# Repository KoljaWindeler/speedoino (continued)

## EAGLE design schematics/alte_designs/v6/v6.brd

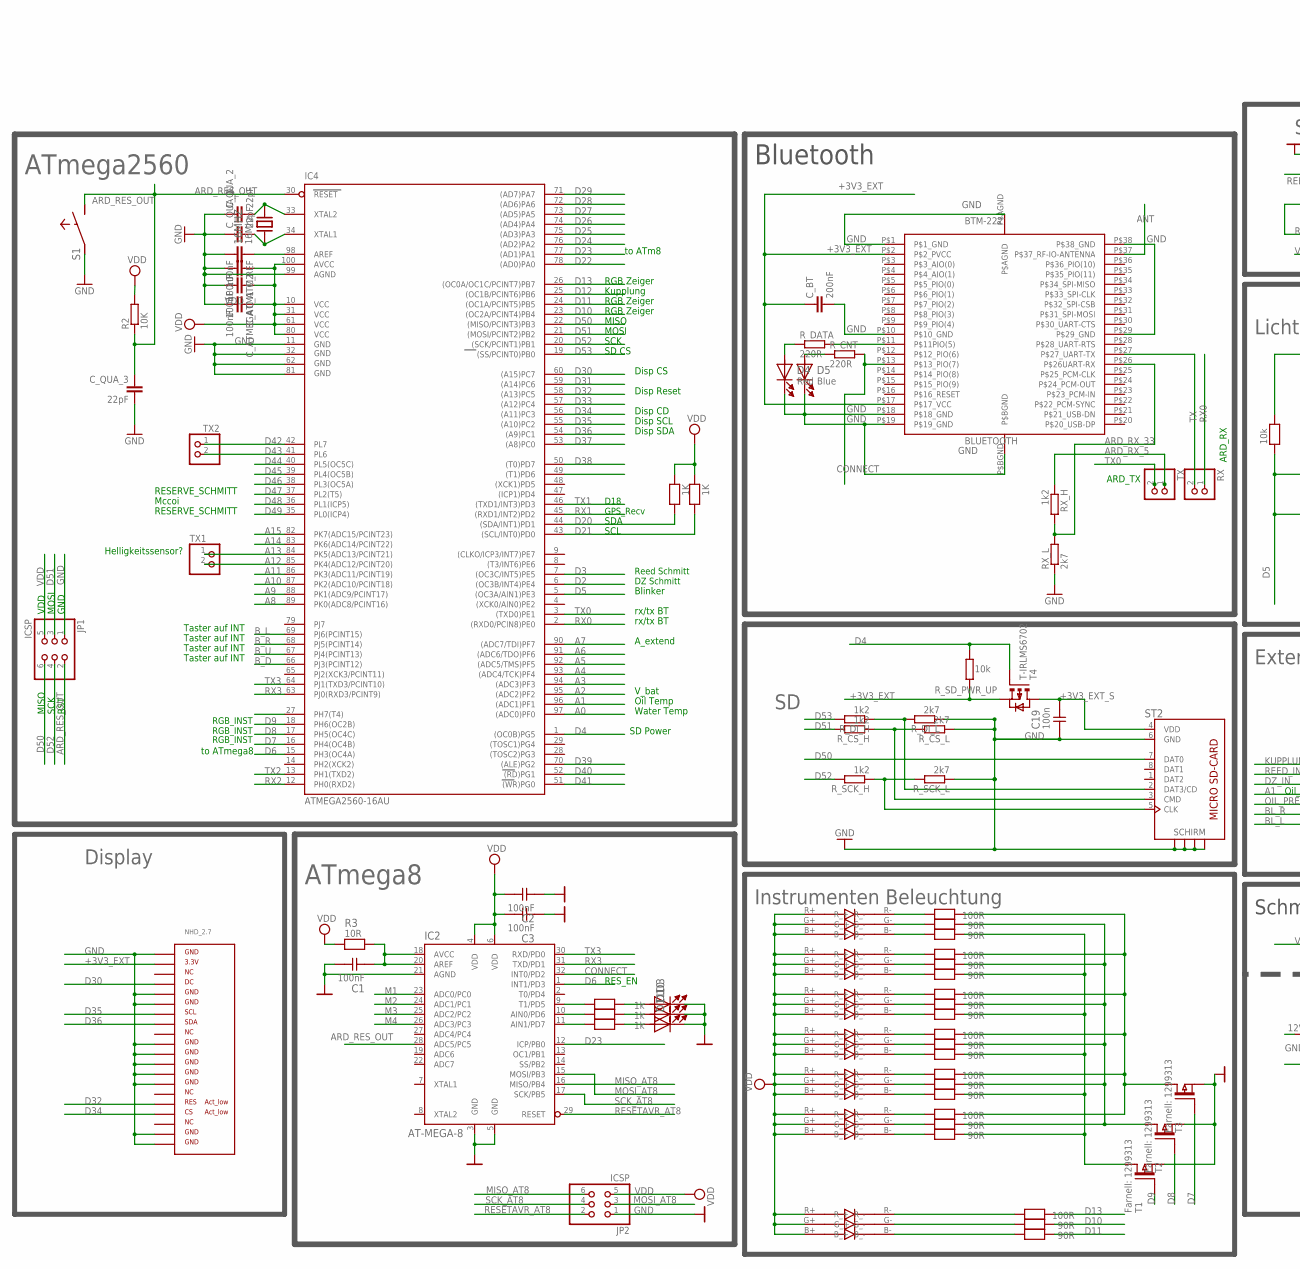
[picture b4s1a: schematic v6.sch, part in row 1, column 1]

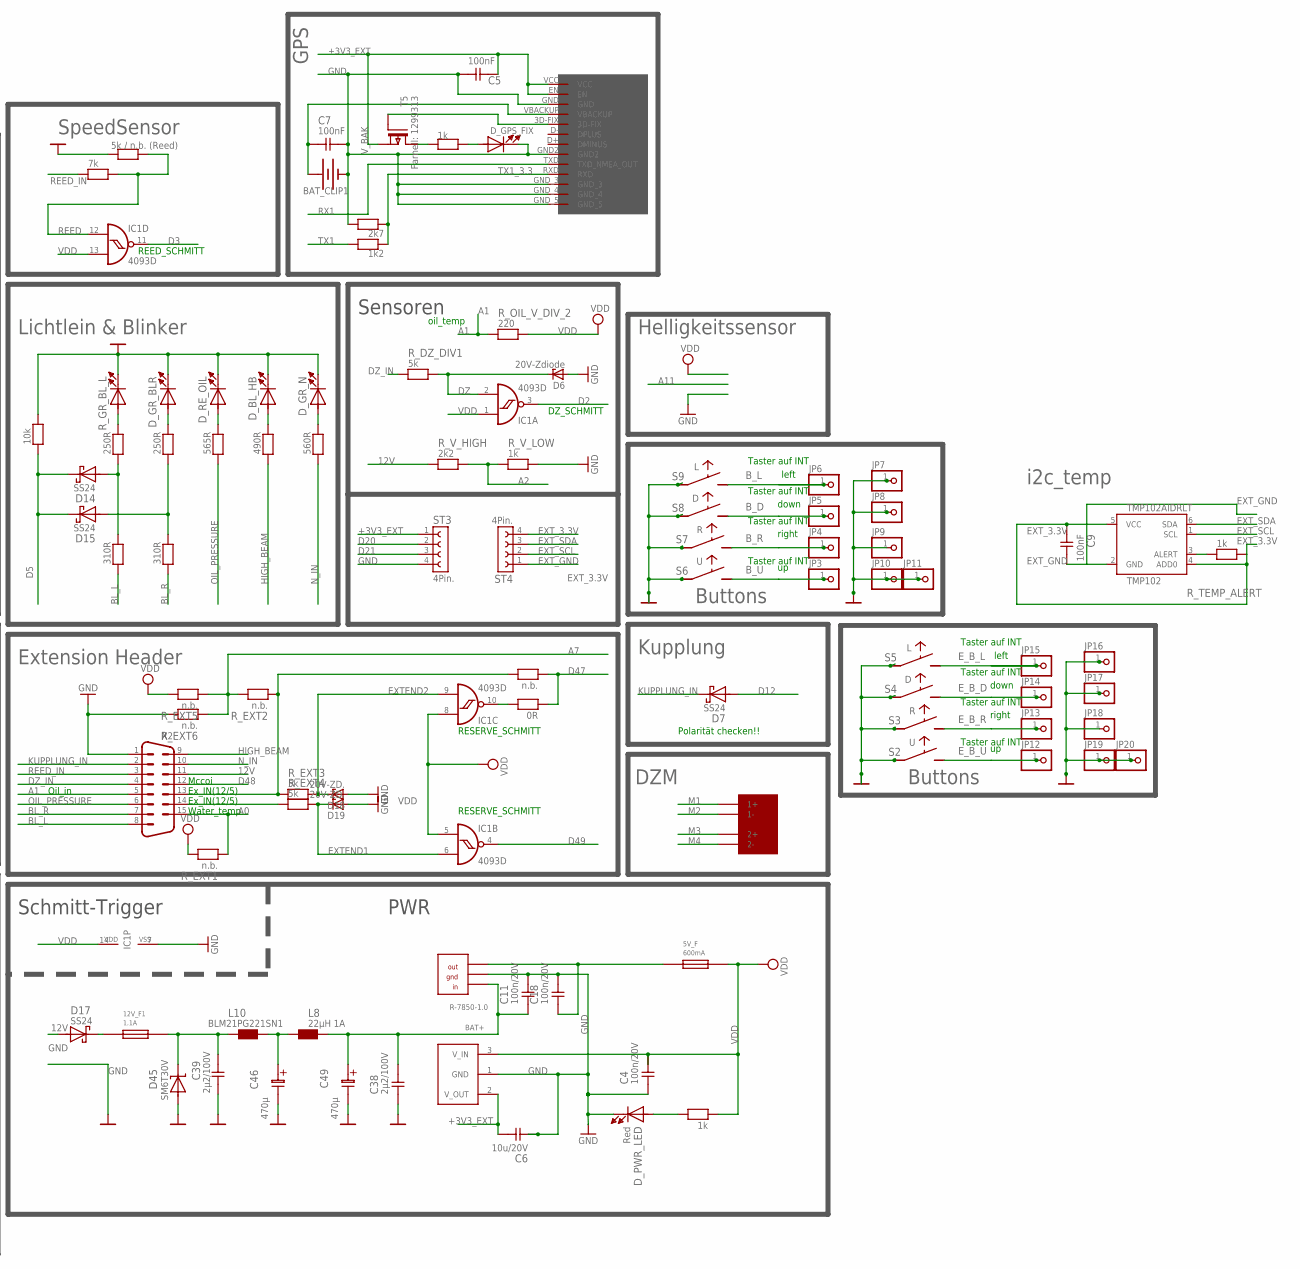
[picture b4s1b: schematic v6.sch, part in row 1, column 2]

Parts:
5V_F: 600mA; POLY_FUSE
12V_F1: 1.1A; POLY_FUSE
16MHZ: 16Mhz; XT-HC49S-SMD
18632422: RGB_LED
BAT_CLIP1: F_908642; BATTCON_12MM
BLUETOOTH: BTM-222
C1, C2, C3, C5, C7, C9: 100nF; 0805
C4, C11, C18: 100n/20V; 0805
C6: 10u/20V; 0805
C19: 100n; 0805
C38, C39: 2µ2/100V; 0805
C46: 470µ; EL-5-8X13R
C49: 470µ; EL-5-8X13
C_ATM1, C_ATM2: 100nF; C0805
C_ATMEGA: 100nF; C0805
C_BT: 200nF; C0805
C_QUA_1, C_QUA_2, C_QUA_3: 22pF; C0805
C_REF: 100nF; C0805
D3, D10, D11: LED0805; LED-0805
D4: Red; LED-0805
D5: Blue; LED-0805
D6: 20V-Zdiode; SMB
D7, D14, D15, D17: SS24; SMB
D18, D19: 20V-ZD.; SMB
D45: SM6T30V; SMB
DCDC53.3: AP1117E33G; SOT223
D_BL_HB: HighB _ 645-598-8191-107F; LED-0805
D_GPS_FIX: Red; LED-0805
D_GR_BLR: BL_R; LED-0805
D_GR_N: N _ M 645-598-8110-107F; LED-0805
D_PWR_LED: Red; LED-0805
D_RE_OIL: OIL M 645-598-8110-107F; LED-0805
GPS: MT3329
IC1: 4093D; SO14
IC2: AT-MEGA-8; TQFP-32_7X7
IC4: ATMEGA2560-16AU; TQFP100
JP1, JP2: ICSP; 2X03
JP3, JP4, JP5, JP6, JP7, JP8, JP9, JP10, JP11, JP12, JP13, JP14, JP15, JP16, JP17, JP18, JP19, JP20: PINHD-1X1; 1X01
L8: 22µH 1A; L-PD54
L10: BLM21PG221SN1; 0805+603
NHD_2.7: NHD_2.7_SOLO_RO
PWR_R78: R-7805-1.0; SIP3
R1, R4: 250R; 0805
R2: 10K; R0805
R3: 10R; 0805
R5: 565R; 0805
R6: 490R; 0805
R7, R8: 310R; 0805
R9: 10k; 0805
R10: 5k / n.b. (Reed); 0805
R11: 7k; 0805
R12, R18, R21, R24, R29, R32, R35: 100R; 0805
R13, R14, R19, R20, R22, R23, R25, R26, R30, R31, R33, R34, R36, R37: 90R; 0805
R15, R16, R17, R28: 1k; 0805
R27: 560R; 0805
R38: 0R; 0805
R39: n.b.; 0805
R40: 2k7; 0805
R41: 1k2; 0805
RX: PINHD-1X2; 1X02
RX_H: 1k2; M0805
RX_L: 2k7; M0805
R_CNT: 220R; M0805
R_CS_H: 1k2; M0805
R_CS_L: 2k7; M0805
R_DATA: 220R; M0805
R_DI_H: 1k2; M0805
R_DI_L: 2k7; M0805
R_DZ_DIV1: 5k; 0805
R_EXT1, R_EXT2, R_EXT5, R_EXT6: n.b.; 0805
R_EXT3, R_EXT4: 5k; 0805
R_GR_BL_L: BL_L; LED-0805
R_LED_5V: 1k; 0805
R_OIL_V_DIV_2: 220; 0805
R_SCK_H: 1k2; M0805
R_SCK_L: 2k7; M0805
R_SCL_UP: 1K; 0805
R_SDA_UP: 1K; 0805
R_SD_PWR_UP: 10k; M0805
R_TEMP_ALERT: 1k; 0805
R_V_HIGH: 2k2; 0805
R_V_LOW: 1k; 0805
S1: SW-TASTERECO-DIAGONAL; SW-ECO
S2, S6: U; SW-ECO
S3, S7: R; SW-ECO
S4, S8: D; SW-ECO
S5, S9: L; SW-ECO
ST2: SD_MICRO
ST3, ST4: BU_1X4_BL17-SMD; BL17SMD_1X4
T1, T2, T3, T5: Farnell: 1299313; SOT-23
T4: T-IRLMS6702; SOT-23-6
TMP102AIDRLT: TMP102; SOT563
TX, TX1, TX2: PINHD-1X2; 1X02
U$3: STEPPER
U$14, U$15, U$16, U$18, U$19, U$20: RGB_LED
X2: SUB-D-IP67; IP67-SUB-D

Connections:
12V: D17.A, R_V_HIGH.1, X2.11
12V_SAFE: 12V_F1.P$2, C39.1, D45.K, L10.1
+3V3_EXT: BLUETOOTH.P$2 (P$2_PVCC), BLUETOOTH.P$17 (P$17_VCC), C5.2, C6.2, C_BT.1, DCDC53.3.2 (V_OUT), GPS.EN, GPS.VCC, NHD_2.7.VDD0 (VDD), R_SD_PWR_UP.2, ST3.1, T4.4 (S), T5.2 (S)
+3V3_EXT_S: C19.2, ST2.4 (VDD), T4.1 (D1), T4.2 (D2), T4.5 (D3), T4.6 (D4)
A0: IC4.97 ((ADC0)PF0), R_EXT1.1, X2.15
A1: IC4.96 ((ADC1)PF1), R_OIL_V_DIV_2.1, X2.5
A2: IC4.95 ((ADC2)PF2), R_V_HIGH.2, R_V_LOW.1
A3: IC4.94 ((ADC3)PF3)
A4: IC4.93 ((ADC4/TCK)PF4)
A5: IC4.92 ((ADC5/TMS)PF5)
A6: IC4.91 ((ADC6/TDO)PF6)
A7: IC4.90 ((ADC7/TDI)PF7), R_EXT2.2, R_EXT5.1, R_EXT6.1
A8: IC4.89 (PK0(ADC8/PCINT16))
A9: IC4.88 (PK1(ADC9/PCINT17))
A10: IC4.87 (PK2(ADC10/PCINT18))
A11: IC4.86 (PK3(ADC11/PCINT19))
A12: IC4.85 (PK4(ADC12/PCINT20)), TX1.2
A13: IC4.84 (PK5(ADC13/PCINT21)), TX1.1
A14: IC4.83 (PK6(ADC14/PCINT22))
A15: IC4.82 (PK7(ADC15/PCINT23))
ANT: BLUETOOTH.P$37 (P$37_RF-IO-ANTENNA)
ARD_RES_OUT: C_QUA_3.1, IC2.28 (ADC5/PC5), IC4.30 (RESET), JP1.2, R2.1, S1.4 (2)
ARD_RX_5: RX_H.1, TX.1
ARD_RX_33: BLUETOOTH.P$26 (P$26UART-RX), RX_H.2, RX_L.2
BAT+: C11.1, C38.2, C49.1, L8.2, PWR_R78.IN
BLUE_INSTR: R14.2, R20.2, R23.2, R31.2, R34.2, R37.2, T1.3 (D)
BL_L: R8.1, X2.8
BL_R: R7.1, X2.7
B_D: IC4.66 (PJ3(PCINT12)), JP5.1, S8.4 (2)
B_L: IC4.69 (PJ6(PCINT15)), JP6.1, S9.4 (2)
B_R: IC4.68 (PJ5(PCINT14)), JP4.1, S7.4 (2)
B_U: IC4.67 (PJ4(PCINT13)), JP3.1, S6.4 (2)
CONNECT: BLUETOOTH.P$13 (P$13_PIO(7)), IC2.32 (INT0/PD2), R_CNT.2
D2: IC1.3 (O), IC4.6 ((OC3B/INT4)PE4)
D3: IC1.11 (O), IC4.7 ((OC3C/INT5)PE5)
D4: IC4.1 ((OC0B)PG5), R_SD_PWR_UP.1, T4.3 (G)
D5: D14.K, D15.K, IC4.5 ((OC3A/AIN1)PE3), R9.2
D6: IC2.1 (INT1/PD3), IC4.15 (PH3(OC4A))
D7: IC4.16 (PH4(OC4B)), T3.1 (G)
D8: IC4.17 (PH5(OC4C)), T2.1 (G)
D9: IC4.18 (PH6(OC2B)), T1.1 (G)
D10: IC4.23 ((OC2A/PCINT4)PB4), R25.2
D11: IC4.24 ((OC1A/PCINT5)PB5), R26.2
D12: D7.A, IC4.25 ((OC1B/PCINT6)PB6)
D13: IC4.26 ((OC0A/OC1C/PCINT7)PB7), R24.2
D20: IC4.44 ((SDA/INT1)PD1), R_SDA_UP.2, ST3.2
D21: IC4.43 ((SCL/INT0)PD0), R_SCL_UP.2, ST3.3
D22: IC4.78 ((AD0)PA0)
D23: IC2.12 (ICP/PB0), IC4.77 ((AD1)PA1)
D24: IC4.76 ((AD2)PA2)
D25: IC4.75 ((AD3)PA3)
D26: IC4.74 ((AD4)PA4)
D27: IC4.73 ((AD5)PA5)
D28: IC4.72 ((AD6)PA6)
D29: IC4.71 ((AD7)PA7)
D30: IC4.60 ((A15)PC7), NHD_2.7.DC
D31: IC4.59 ((A14)PC6)
D32: IC4.58 ((A13)PC5), NHD_2.7.RES
D33: IC4.57 ((A12)PC4)
D34: IC4.56 ((A11)PC3), NHD_2.7.CS
D35: IC4.55 ((A10)PC2), NHD_2.7.SCLK (SCL)
D36: IC4.54 ((A9)PC1), NHD_2.7.SDIN (SDA)
D37: IC4.53 ((A8)PC0)
D38: IC4.50 ((T0)PD7)
D39: IC4.70 ((ALE)PG2)
D40: IC4.52 ((RD)PG1)
D41: IC4.51 ((WR)PG0)
D42: IC4.42 (PL7), TX2.1
D43: IC4.41 (PL6), TX2.2
D44: IC4.40 (PL5(OC5C))
D45: IC4.39 (PL4(OC5B))
D46: IC4.38 (PL3(OC5A))
D47: IC4.37 (PL2(T5)), R38.2, R39.2
D48: IC4.36 (PL1(ICP5)), X2.12
D49: IC1.4 (O), IC4.35 (PL0(ICP4))
D50: IC4.22 ((MISO/PCINT3)PB3), JP1.6, ST2.7 (DAT0)
D51: IC4.21 ((MOSI/PCINT2)PB2), JP1.3, R_CS_H.2
D52: IC4.20 ((SCK/PCINT1)PB1), JP1.4, R_SCK_H.2
D53: IC4.19 ((SS/PCINT0)PB0), R_DI_H.2
DZ: D6.C, IC1.2 (I1), R_DZ_DIV1.2
DZ_IN: R_DZ_DIV1.1, X2.4
EXTEND1: D19.C, IC1.6 (I1), R_EXT4.2
EXTEND2: D18.C, IC1.9 (I1), R_EXT3.2
EXT_3.3V: C9.1, R_TEMP_ALERT.2, ST4.4, TMP102AIDRLT.4 (ADD0), TMP102AIDRLT.5 (VCC)
EXT_GND: C9.2, ST4.1, TMP102AIDRLT.2 (GND)
EXT_SCL: ST4.2, TMP102AIDRLT.1 (SCL)
EXT_SDA: ST4.3, TMP102AIDRLT.6 (SDA)
E_B_D: JP14.1, S4.4 (2)
E_B_L: JP15.1, S5.4 (2)
E_B_R: JP13.1, S3.4 (2)
E_B_U: JP12.1, S2.4 (2)
E_GND: JP16.1, JP17.1, JP18.1, JP19.1, JP20.1, S2.1, S3.1, S4.1, S5.1
GND: BAT_CLIP1.GND (-), BLUETOOTH.P$1 (P$1_GND), BLUETOOTH.P$10 (P$10_GND), BLUETOOTH.P$18 (P$18_GND), BLUETOOTH.P$19 (P$19_GND), BLUETOOTH.P$29 (P$29_GND), BLUETOOTH.P$38 (P$38_GND), BLUETOOTH.P$AGND, BLUETOOTH.P$BGND, C1.2, C2.1, C3.1, C4.1, C5.1, C6.1, C7.2, C11.2, C18.2, C19.1, C38.1, C39.2, C46.2, C49.2, C_ATM1.2, C_ATM2.2, C_ATMEGA.2, C_BT.2, C_QUA_1.1, C_QUA_2.1, C_QUA_3.2, C_REF.2, D3.2 (K), D4.2 (K), D5.2 (K), D6.A, D10.2 (K), D11.2 (K), D18.A, D19.A, D45.A, DCDC53.3.1 (GND), D_BL_HB.2 (K), D_GPS_FIX.2 (K), D_GR_BLR.2 (K), D_GR_N.2 (K), D_PWR_LED.2 (K), D_RE_OIL.2 (K), GPS.GND, GPS.GND2, GPS.GND_3, GPS.GND_4, GPS.GND_5, IC1.7 (VSS), IC2.3 (GND), IC2.5 (GND), IC2.21 (AGND), IC4.11 (GND), IC4.32 (GND1), IC4.62 (GND2), IC4.81 (GND3), IC4.99 (AGND), JP1.1, JP2.1, JP7.1, JP8.1, JP9.1, JP10.1, JP11.1, NHD_2.7.GND0 (GND), NHD_2.7.GND1 (GND2), NHD_2.7.GND2 (GND3), NHD_2.7.GND3 (GND4), NHD_2.7.GND4 (GND5), NHD_2.7.GND5 (GND6), NHD_2.7.GND6 (GND7), NHD_2.7.GND7 (GND8), NHD_2.7.GND8 (GND9), NHD_2.7.GND9 (GND10), PWR_R78.GND, R9.1, R10.2, R40.2, RX_L.1, R_CS_L.1, R_DI_L.1, R_EXT6.2, R_GR_BL_L.2 (K), R_SCK_L.1, R_V_LOW.2, S1.1, S6.1, S7.1, S8.1, S9.1, ST2.6 (GND), ST2.GND (SCHIRM1), ST2.GND2 (SCHIRM2), ST2.GND3 (SCHIRM3), ST2.GND4 (SCHIRM), ST3.4, T1.2 (S), T2.2 (S), T3.2 (S), X2.1
GREEN_INSTR: R13.2, R19.2, R22.2, R30.2, R33.2, R36.2, T2.3 (D)
HIGH_BEAM: R6.1, X2.9
KUPPLUNG_IN: D7.K, X2.2
M1: IC2.23 (ADC0/PC0), U$3.1+
M2: IC2.24 (ADC1/PC1), U$3.1-
M3: IC2.25 (ADC2/PC2), U$3.2+
M4: IC2.26 (ADC3/PC3), U$3.2-
MISO_AT8: IC2.16 (MISO/PB4), JP2.6
MOSI_AT8: IC2.15 (MOSI/PB3), JP2.3
unnamed: C46.1, L8.1, L10.2
unnamed: D14.A, R1.1, R8.2
unnamed: C1.1, IC2.18 (AVCC), IC2.20 (AREF), R3.2
unnamed: R_TEMP_ALERT.1, TMP102AIDRLT.3 (ALERT)
unnamed: D5.1 (A), R_CNT.1
unnamed: R31.1, U$18.B- (B_-)
unnamed: R30.1, U$18.G- (G_-)
unnamed: R29.1, U$18.R- (R_-)
unnamed: D_PWR_LED.1 (A), R_LED_5V.2
unnamed: R34.1, U$16.B- (B_-)
unnamed: D15.A, R4.1, R7.2
unnamed: D4.1 (A), R_DATA.1
unnamed: R_CS_H.1, R_CS_L.2, ST2.3 (CMD)
unnamed: IC2.11 (AIN1/PD7), R17.1
unnamed: D_GPS_FIX.1 (A), R28.2
unnamed: GPS.3D-FIX, T5.1 (G)
unnamed: R28.1, T5.3 (D)
unnamed: IC2.10 (AIN0/PD6), R16.1
unnamed: 5V_F.P$1, C18.1, PWR_R78.OUT
unnamed: IC2.9 (T1/PD5), R15.1
unnamed: R33.1, U$16.G- (G_-)
unnamed: R32.1, U$16.R- (R_-)
unnamed: R_SCK_H.1, R_SCK_L.2, ST2.5 (CLK)
unnamed: 12V_F1.P$1, D17.K
unnamed: R_DI_H.1, R_DI_L.2, ST2.2 (DAT3/CD)
unnamed: R37.1, U$14.B- (B_-)
unnamed: R36.1, U$14.G- (G_-)
unnamed: R35.1, U$14.R- (R_-)
unnamed: R1.2, R_GR_BL_L.1 (A)
unnamed: D_GR_BLR.1 (A), R4.2
unnamed: 16MHZ.2, C_QUA_2.2, IC4.33 (XTAL2)
unnamed: 16MHZ.1, C_QUA_1.2, IC4.34 (XTAL1)
unnamed: C_REF.1, IC4.98 (AREF)
unnamed: D_RE_OIL.1 (A), R5.2
unnamed: D_BL_HB.1 (A), R6.2
unnamed: IC1.10 (O), R38.1
unnamed: R12.1, U$15.R- (R_-)
unnamed: R13.1, U$15.G- (G_-)
unnamed: R14.1, U$15.B- (B_-)
unnamed: 18632422.R- (R_-), R18.1
unnamed: 18632422.G- (G_-), R19.1
unnamed: 18632422.B- (B_-), R20.1
unnamed: R21.1, U$19.R- (R_-)
unnamed: R22.1, U$19.G- (G_-)
unnamed: R23.1, U$19.B- (B_-)
unnamed: R24.1, U$20.R- (R_-)
unnamed: R25.1, U$20.G- (G_-)
unnamed: R26.1, U$20.B- (B_-)
unnamed: D_GR_N.1 (A), R27.2
unnamed: R_EXT4.1, X2.14
unnamed: R39.1, R_EXT2.1, R_EXT3.1, X2.13
N_IN: R27.1, X2.10
OIL_PRESSURE: R5.1, X2.6
P0: D3.1 (A), R15.2
P1: D10.1 (A), R16.2
P2: D11.1 (A), R17.2
RED_INSTR: R12.2, R18.2, R21.2, R29.2, R32.2, R35.2, T3.3 (D)
REED: IC1.12 (I0), R10.1, R11.2
REED_IN: R11.1, X2.3
RESETAVR_AT8: IC2.29 (RESET), JP2.2
RX0: IC4.2 ((RXD0/PCIN8)PE0), RX.1
RX1: GPS.TXD (TXD_NMEA_OUT), IC4.45 ((RXD1/INT2)PD2)
RX2: IC4.12 (PH0(RXD2))
RX3: IC2.31 (TXD/PD1), IC4.63 (PJ0(RXD3/PCINT9))
SCK_AT8: IC2.17 (SCK/PB5), JP2.4
TO_DATA_LED: BLUETOOTH.P$11 (P$11PIO(5)), R_DATA.2
TX: BLUETOOTH.P$27 (P$27_UART-TX), RX.2
TX0: IC4.3 ((TXD0)PE1), TX.2
TX1: IC4.46 ((TXD1/INT3)PD3), R41.2
TX1_3.3: GPS.RXD, R40.1, R41.1
TX2: IC4.13 (PH1(TXD2))
TX3: IC2.30 (RXD/PD0), IC4.64 (PJ1(TXD3/PCINT10))
VDD: 5V_F.P$2, 18632422.B+ (B_+), 18632422.G+ (G_+), 18632422.R+ (R_+), C2.2, C3.2, C4.2, C_ATM1.1, C_ATM2.1, C_ATMEGA.1, DCDC53.3.3 (V_IN), IC1.1 (I0), IC1.5 (I0), IC1.8 (I0), IC1.13 (I1), IC1.14 (VDD), IC2.4 (VDD), IC2.6 (VDD), IC4.10 (VCC), IC4.31 (VCC1), IC4.61 (VCC2), IC4.80 (VCC3), IC4.100 (AVCC), JP1.5, JP2.5, R2.2, R3.1, R_EXT1.2, R_EXT5.2, R_LED_5V.1, R_OIL_V_DIV_2.2, R_SCL_UP.1, R_SDA_UP.1, U$14.B+ (B_+), U$14.G+ (G_+), U$14.R+ (R_+), U$15.B+ (B_+), U$15.G+ (G_+), U$15.R+ (R_+), U$16.B+ (B_+), U$16.G+ (G_+), U$16.R+ (R_+), U$18.B+ (B_+), U$18.G+ (G_+), U$18.R+ (R_+), U$19.B+ (B_+), U$19.G+ (G_+), U$19.R+ (R_+), U$20.B+ (B_+), U$20.G+ (G_+), U$20.R+ (R_+)
V_BAK: BAT_CLIP1.PWR@1 (+), C7.1, GPS.VBACKUP

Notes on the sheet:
Schmitt-Trigger
PWR
Sensoren
Bluetooth
Buttons
MOSI
SCK
MISO
SDA
SCL
left
down
right
DZ_SCHMITT
REED_SCHMITT
RESERVE_SCHMITT
oil_temp
ATmega2560
D18
Extension Header
GND
VDD
RST
RES_EN
ARD_RX
ARD_TX
i2c_temp
ATmega8
Lichtlein & Blinker
SpeedSensor
Instrumenten Beleuchtung
RGB_INST
Reed Schmitt
DZ Schmitt
GPS
GPS_Recv
Display
DZM
to ATm8
Oil Temp

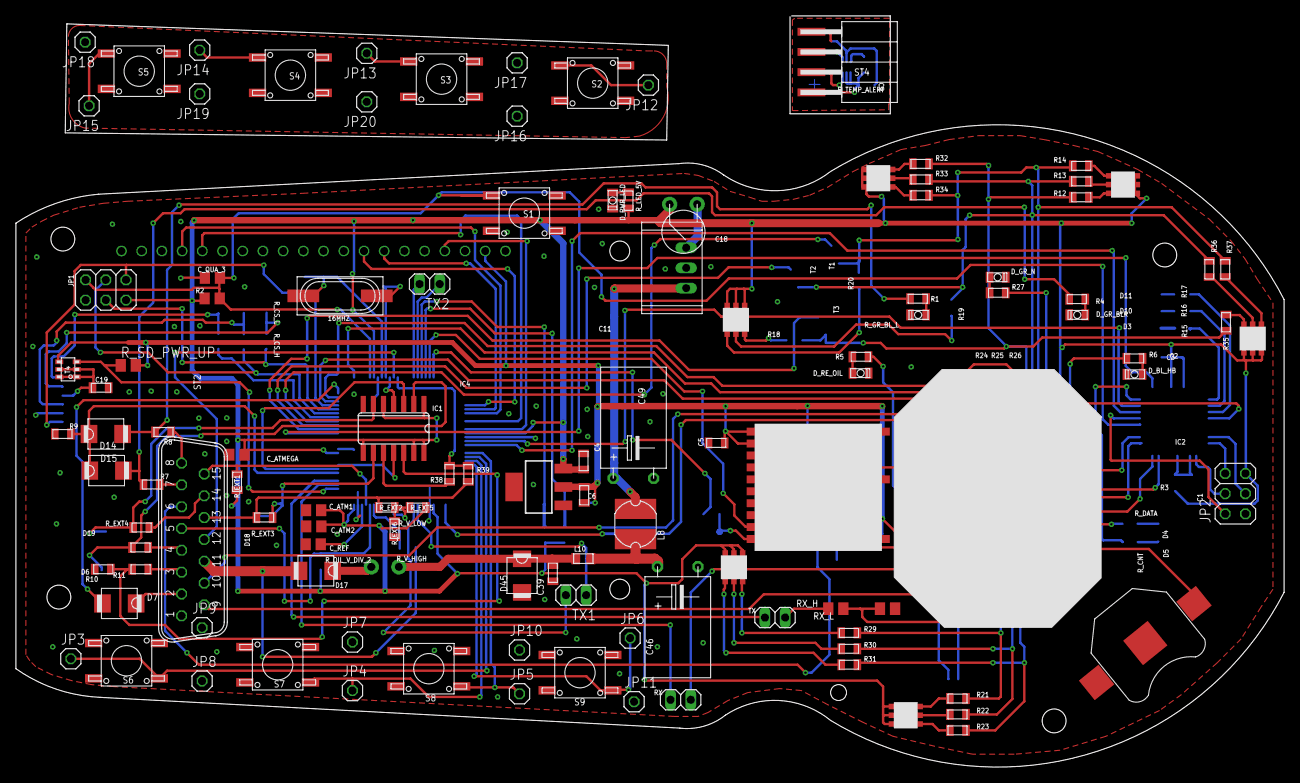
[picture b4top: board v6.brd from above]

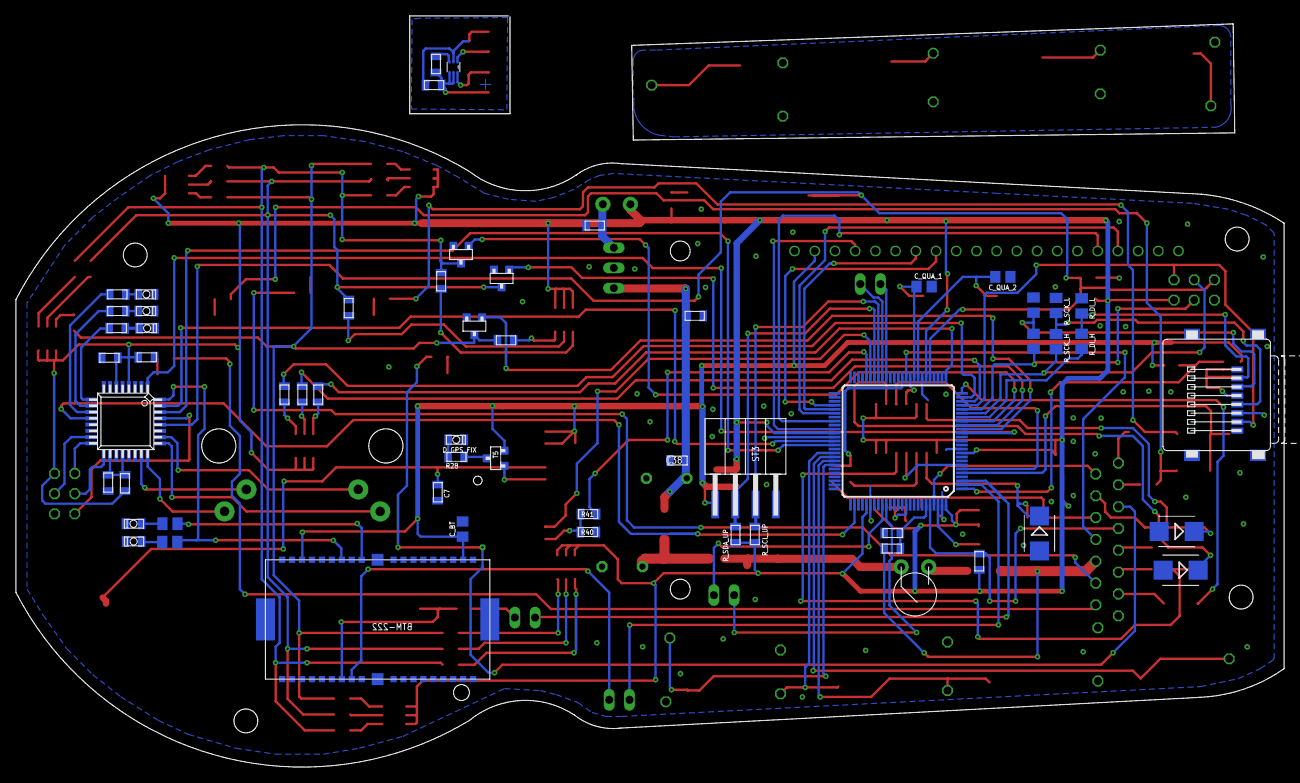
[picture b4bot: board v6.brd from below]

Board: 2 copper layers, 159.4 x 80.7 mm, 174 parts (58 on the bottom side), 146 nets.

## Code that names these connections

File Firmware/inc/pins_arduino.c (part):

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// ATMEL ATMEGA8 & 168 / ARDUINO
//
//                  +-\/-+
//            PC6  1|    |28  PC5 (AI 5)
//      (D 0) PD0  2|    |27  PC4 (AI 4)
//      (D 1) PD1  3|    |26  PC3 (AI 3)
//      (D 2) PD2  4|    |25  PC2 (AI 2)
// PWM+ (D 3) PD3  5|    |24  PC1 (AI 1)
//      (D 4) PD4  6|    |23  PC0 (AI 0)
//            VCC  7|    |22  GND
//            GND  8|    |21  AREF
//            PB6  9|    |20  AVCC
//            PB7 10|    |19  PB5 (D 13)
// PWM+ (D 5) PD5 11|    |18  PB4 (D 12)
// PWM+ (D 6) PD6 12|    |17  PB3 (D 11) PWM
//      (D 7) PD7 13|    |16  PB2 (D 10) PWM
//      (D 8) PB0 14|    |15  PB1 (D 9) PWM
//                  +----+
//
// (PWM+ indicates the additional PWM pins on the ATmega168.)

// ATMEL ATMEGA1280 / ARDUINO
//
// 0-7 PE0-PE7   works
// 8-13 PB0-PB5  works
// 14-21 PA0-PA7 works 
// 22-29 PH0-PH7 works
// 30-35 PG5-PG0 works
// 36-43 PC7-PC0 works
// 44-51 PJ7-PJ0 works
// 52-59 PL7-PL0 works
// 60-67 PD7-PD0 works
// A0-A7 PF0-PF7
// A8-A15 PK0-PK7

#define PA 1
#define PB 2
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
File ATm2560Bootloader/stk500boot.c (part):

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//************************************************************************
// init display
static void init_display(void){
	DDRC = 0x00 | (1<<PC7) | (1<<PC5) | (1<<PC3) | (1<<PC2) | (1<<PC1);

	_delay_ms(1); // TODO: Change to 1 ?

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	unsigned int	boot_state;

	/////////Kolja von hier/////////
	/* enabled in ph3 to read if its a bluetooth reset*/
	DDRH  &= ~(1<<PH3); // one input
	PORTH =  0x00 | (1<<PH3); // with pullup

	/* enabled pull up on CAN CS connection, to deactivate can bus interface (interface is low active)*/
	PORTK |= (1<<PK4);
	/////////Kolja bis hier/////////


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
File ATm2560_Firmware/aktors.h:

/*
 * aktors.h
 *
 *  Created on: 16.11.2011
 *      Author: jkw
 */

#ifndef AKTORS_H_
#define AKTORS_H_

#define RGB_ACTION_TYPE_STATIC 0
#define RGB_ACTION_TYPE_FOLLOW 1
#define RGB_ACTION_TYPE_STACK 2
#define RGB_ACTION_TYPE_RSTACK 3

#define RGB_OUT_R_PIN PH4		// 7
#define RGB_OUT_R_PORT PORTH
#define RGB_OUT_R_DIR DDRH

#define RGB_OUT_G_PIN PH5		// 8
#define RGB_OUT_G_PORT PORTH
#define RGB_OUT_G_DIR DDRH

#define RGB_OUT_B_PIN PH6		// 9
#define RGB_OUT_B_PORT PORTH
#define RGB_OUT_B_DIR DDRH

#define RGB_IN_W_PIN PB7		// 13
#define RGB_IN_W_PORT PORTB
#define RGB_IN_W_DIR DDRB

#define RESET_KICK_TO_RESET 0x01
#define RESET_COMPLETE 0x02
#define RESET_PREPARE 0x03

#define ATM328RESETPIN PD4
#define PORT_REP_ADDR 0x20				// I2C Address of MCP23017 Chip
#define PORT_REP_ADDR_GPIO_A 0x12     // Register Address of Port A
#define PORT_REP_ADDR_GPIO_B 0x13     // Register Address of Port B
#define FLASHER_RIGHT 3 // bit in register
#define HIGH_BEAM 4 // bit in register
#define NEUTRAL_GEAR 5 // bit in register
#define FLASHER_LEFT 6 // bit in register
#define OIL 7 // bit in register

#define FLASH_COLOR_REACHED 0	// dimm states
#define DIMM_TO_FLASH_COLOR 1
#define STATIC_COLOR_REACHED 2
#define DIMM_TO_STATIC_COLOR 3
#define DIMM_TO_DARK 4
#define MIN_REACHED 5
#define MAX_REACHED 6



typedef struct{
	uint8_t actual;
	uint8_t from;
	uint8_t to;
} led_values;

typedef struct{
	uint8_t r;
	uint8_t g;
	uint8_t b;
} led_simple;

typedef struct{
	led_values r;
	led_values g;
	led_values b;
} led;



class Speedo_aktors{
public:
	Speedo_aktors(void);
	~Speedo_aktors();
	void init();
	bool check_vars();
	void set_rgb_in(int r,int g,int b);
	void set_rgb_in(int r,int g,int b,int save);
	void set_rgb_out(int r,int g,int b);
	void set_rgb_out(int r,int g,int b,int save);
	void dimm_rgb_to(int r,int g,int b,int max_dimm_steps);
	void timer_overflow();
	void run_reset_on_ATm328(char mode);
	bool dimm_available();
	int  update_outer_leds(bool dimm,bool overwrite);
	int set_bt_pin();
	void check_flag();
	bool check_mac_key(uint8_t* result,bool* comm_error);
	int ask_bt(char *command);
	int ask_bt(char *buffer, bool answere_needed, int8_t max_length, uint8_t* char_rec);
	void stop_dimmer();
	void set_active_dimmer(bool state);
	int set_expander();
	int set_controll_lights(uint8_t oil,uint8_t flasher_left,uint8_t n_gear,uint8_t flasher_right,uint8_t high_beam, bool now);
	int set_rbg_active(int status, bool now);
	void rgb_action(int needle_pos);
	speedo_stepper* m_stepper;
	speedo_oiler* m_oiler;
	led RGB;
	led_simple dz_flasher,oil_start_color,oil_end_color,water_start_color,water_end_color,kmh_start_color,kmh_end_color,dz_start_color,dz_end_color,static_color;
	int8_t led_mode,pointer_highlight_mode;
	int oil_max_value,oil_min_value,water_max_value,water_min_value,kmh_max_value,kmh_min_value,dz_max_value,dz_min_value,bt_pin;
	bool attention_required;

private:
	int current_sensor_value;
	int dimm_steps,dimm_step;
	short int dimm_state;
	bool colorfade_active;
	bool expander_outdated;
	uint8_t control_lights;
	uint8_t led_area_controll;

};
extern Speedo_aktors* pAktors;

#endif /* AKTORS_H_ */

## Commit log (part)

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2013-04-03 Lang
2013-04-03 Remove build files
2013-04-03 added git ignore to ATm328 Firmware
2013-04-03 SkinEditor rebuild
2013-04-07 Keep alive fkt added to draw current from "dauer +"
2013-04-07 Added GPS Symbol
2013-04-07 Added debug output of filename to write
2013-04-07 Write GPS Points to SD only on motor running
2013-04-07 Added multiple can scans
2013-04-07 Sending infor request only if in OBD2 mode
2013-04-07 Timer polls Lights
2013-04-07 Formating
2013-04-09 Added CAN Filter for triumph. Up and running
2013-04-09 Correct use of getFailure in Speedo
2013-04-09 Avoid Input check if in Triumph mode (to heavy)
2013-04-09 Added Speedo1v11 as stable Added new Version Speedoino1v12 with CAN filter, indicator support, dual buffer, MIL suppression on engine stop as testing
2013-04-09 Added Menu to select CAN type
2013-04-10 Moved Speedoino _1v12 as stable Added low pass filter and Speed suppression Removed CAN polling
2013-04-10 Board equiped with low passes
2013-04-12 Set SPI to 1Mhz
2013-04-14 Rewritten the Power Managment
2013-04-14 Improved Clock setting by GPS
2013-04-14 Added "we are on ignition" message after clock mode power up
2013-04-15 Moved interrupt init to CAN and reactivated set bt pin
2013-04-17 Added "go_to_bootloader" commands
2013-04-23 Added next Gear in calibration mode to calibrate all gear easier
2013-04-23 Change demomode
2013-04-23 Added comments and defines
2013-04-28 Added debug loop output
2013-04-28 Added webpage
2013-05-05 Return CAN_TYPE_NONE if can is not active, to be able to just ask the cantype ..
2013-05-05 Added verification to "firmware" upload
2013-05-05 Trying to find the reason for the resets, not sure about the connection to the temperature sensor anymore
2013-05-05 Added centering of the Warning messeages
2013-05-20 Added "ask for title" on generating navifile
2013-06-03 Modified: Dont set Lights within interrupt. Set flag and check that periodicaly
2013-06-03 Modified: Renamed "NonPermanent" to "From Start"
2013-06-08 updated PINtext
2013-06-13 Rebuild Atmega328 Bootloader
2013-06-16 Added sub_dir support to SpeedoAndroid Download Tab
2013-06-16 Added Subdir for GPS Files
2013-06-16 enabled CAN debug
2013-06-16 Added check to ensure the "center string" is not longer than the space to write it in
2013-06-16 Modified to CAN warning message
2013-06-18 Added "Auto Scan" for Animation
2013-06-19 First integration of demo class, unstable
2013-06-19 Demo Class added, ATm328 Bootloader unable to verify... mummbel mummbel
2013-06-20 Fixed: Next gear calibration after last finished Added: Demo Mode nearly working Bug detected: Add info line is not refreshing in the right interval
2013-06-21 Fiexed App Bug, to loose the current dir while deleting a file
2013-06-21 Released Version 2.1
2013-06-24 Removed CAN mal as Addinfo for Triumpf CAN bus
2013-06-27 Added improved mountpoint for the filemanager based animations
2013-06-30 avoid programming if messages are longer than 128k
2013-06-30 Comments added
2013-07-09 Improved display mode of Log file.
2013-07-09 Modified GPS log files, save two digits for sat count
2013-07-12 Added GPS reconfigure command, if there is no incoming messages from the GPS within the first ten seconds
2013-07-14 to avoid that all timers run in the same loop I added some starttimes to them
2013-07-14 Added GPS comandset doku
2013-07-14 increased RPM calculation to 10Hz (was 5Hz) -> calc + goto
    lets see if that leads to a better reacting stepper
2013-07-14 Added load_calculation and corrected some comments
2013-07-14 Reduced freq of gga to 20%
2013-07-14 Added Laptimer caption
2013-07-14 Recompiled with stepper support
2013-07-16 Initial Release of LapTimer Interface not yet ready
2013-07-18 Reworked show_storry to support PSTR
2013-07-18 Added return ms timestamp
2013-07-18 Reset blinker distace if speed=0
2013-07-18 capture interface
2013-07-20 Changed get_file_handle to work without the leading two byte ..
2013-07-20 Ready for a first try version of the laptimer
2013-07-20 Testing version with laptimer added
2013-07-20 Testing version with laptimer added..
2013-07-21 Removed strings
2013-07-21 improved clock setting
2013-07-21 Removed upload filename bug
2013-07-21 get filename from clock and check return value improved
2013-07-22 modified get_order to return status
2013-07-23 Updated a lot of stuff
2013-07-24 Working at first test very good
2013-07-24 Added debug + tempfiles
2013-07-26 More checks before return the date
2013-07-26 reinit display before and after animation
2013-07-27 fixed GPS filename generation
2013-07-28 Added settings tab to AndroidApp, to disable verifying by checking/unchecking
2013-07-28 Neue Firmware zum Testen + Android App
2013-07-28 Fixed upload file
2013-07-29 Added lapcounter to show last laptime for a while
2013-07-29 Fixxed DOwnload issue
2013-07-29 New Testing Version upload
2013-07-30 Added shorter, easier version of get_file_handle as overloaded funktion
2013-07-30 Updated SD Files
2013-07-30 Added low pass to reed signal, have to check the correct value (200nF?)
2013-07-31 Added new mode to show_storry
2013-07-31 Uploaded new testing Version
2013-07-31 Reworked LapTimer to use "real" Bestlap and not theoretical (although both modes are in the code, just the "real" is active by now). Maybe a settings menu will be added
2013-07-31 Added App generates Path's to every log file + Seperator per lap for the race mode
2013-08-01 Updated new version
2013-08-04 Added decoding of compressed gps logs to android app
2013-08-04 Reduced memory usage of the startup var from 200 to 30 bytes
2013-08-04 Added filter for weak gps points
2013-08-08 Added vars to log file
2013-08-08 Reduced buffer size of the startup var
2013-08-08 Increased speed of RPM update very much
2013-08-08 added more debug to the laptimer
2013-08-08 Added testing version
2013-08-12 Switched back to uncompressed format to check if this is the reason for the sometimes wrong date
2013-08-12 added "force" mode to overwrite timeout of calc()
2013-08-12 Improved Voltage calculation to 2 digits behind comma
2013-08-12 Increased freq from 10 to 40Hz to controll the step motor faster, activated for CAN as well as for sensors
2013-08-13 Reduced time to fade back after RPM warning from 2s to 250ms
2013-08-13 Added menu to switch between real/calculated laptime
2013-08-13 Increased Low passing
2013-08-13 Added Blinking, fixed Time calc of best time
2013-08-13 Updated Releases
2013-08-14 Laptmer Time Bug fixed
2013-08-14 + RAM optimised (short to int8_t) + Moved a lot of values from EEPROM to SD Card + Display checks vars befor init is done (safety)
2013-08-14 New Version added
2013-08-15 First proof-of-concept of SpeedCams
2013-08-17 Moved structs to global.h
2013-08-17 Added SpeedCam displaying to SpeedoMainScreen
2013-08-17 Removed debugging
2013-08-17 First Alpha Version of the SpeedCam Module
2013-08-17 Improved handling of "file not available"
2013-08-18 Turn RGB Leds to Flasher Color, if a POI is near
2013-08-18 Extended set_gps_status to have minimum 15km/h instead of 10km/h
2013-08-18 Added MenuState to show SpeedCam status
2013-08-18 Added set_drive_status() to calc() to reset the time of driving .. avoid REED ERROR displaying
2013-08-18 Added SCDB POI.TXT Status July 2013
2013-08-18 Improved Bootscreen output
2013-08-19 Fixed unsinged to int bug
2013-08-19 moved gps_goodies to gps
2013-08-19 Fixed displaying options in main speedo
2013-08-19 Added first POI_finder approach
2013-08-19 Added file_select menu for poi finder
2013-08-20 POI finder: added file parsing, crashes on writing to file, or later, don't know by now
2013-08-21 + Moved SendString to use PSTR to save memory + Change "end-of-line" detection to 0x0A
2013-08-21 Fire addition "stepper-goto" only if differ is >1000 ... was 500
2013-08-21 First possibly running version of the POI finder
2013-08-22 SpeedoApp added upload of POI files to POI directory using the upload config button
2013-08-22 Modified the way to get the analog RPM, should avoid the bouncing
2013-08-22 New Version upload
2013-08-22 fixed return to zero
2013-08-22 Increase extra RPM fire likelyhood .. faster reaction
2013-08-22 Version upgrade
2013-08-27 Added Get BT Key
2013-08-27 reduced distance
2013-08-27 Check rebase
2013-08-28 Removed conditional fire ... fire every 25ms (Stepper pos) For testing
2013-08-28 Fixed reset loop
2013-09-02 Added RGB action -> highlight the needle with the rgb LEDs
2013-09-02 Added support for RGB action
2013-09-02 Formating and gap fixing
2013-09-02 Added TMC222
2013-09-02 Added new Version
2013-09-05 Fixed distance calc bug: cast to unsigned long to get squares
2013-09-05 Added set_value_dialog, first version. Select CAN source crashes!
2013-09-05 Bug fix to fade color back after attention was needed
2013-09-05 Reenabled buttons on "show storry"
2013-09-05 Removed "reset over interrupt" code for hardware version 6
2013-09-05 Added "return 0" to gps sat count if the last valid sample is older than 3 sec
2013-09-08 Added Status keeper: update the port extender only if the status differs
2013-09-08 Added Checksum test on incoming NMEA datasentences. Removed the "squared" returnment.
2013-09-08 Added limit file and inserted the LONG_MAX define in the max distance calculation
2013-09-08 Housekeeping: Added defines
2013-09-08 housekeeping
2013-09-12 First Version with stepper tmc222 support
2013-09-15 Stepper commands added
2013-09-15 Set I2C speed to high to communicate with the stepper driver
2013-09-21 init + run + reduced current
2013-09-21 Just runs with THIS current settings
2013-09-26 changing to real timer rate
2013-09-29 Added feedbackinfo to "ask mac key" Modified "ask bt" to work with two independend buffers
2013-09-29 Added Macro to get high and low byte
2013-09-29 Added Calibration command and removed under voltage controll for a while
2013-09-29 Added Pullups to the input lines
2013-09-29 Reduced speed of the stepper
2013-09-30 Version update
2013-10-01 Corrected parameter for the 6405
2013-10-03 Fixed Wintertime Bug
2013-10-04 Removed TMC222
2013-10-04 Added stepper RPM var
2013-10-08 Removed useless pins
2013-10-08 Moved all vars from 16 to 8 Bit
2013-10-08 Moved away from Arduino pinMode
2013-10-08 combined sensor pull_value
2013-10-08 removed useless calls of RPM calc functions
2013-10-09 Moving digitalWrite to basic functions
2013-10-09 Moved from timer5 to timer1, as timer5 might be needed for high speed wheel impuses
2013-10-09 corrected pin low function
2013-10-10 new build
2013-10-10 Added speed and accel to reset.h and added new commands to run in self mode
2013-10-10 Added stepper mode var for development reasons
2013-10-12 Added great running PID filter for RPM detection
2013-10-12 Removed TMC222 Code
2013-10-12 Removed stepper value .. stepper now shows direct value (the values comes filtered by the dz class)
2013-10-12 Removed "helper" diodes for the GPS module... they discharged the gps battery
2013-10-19 Added STm32 CodeBase
2013-10-19 temp
2013-10-19 Added STm32
2013-10-21 Added Display approach
2013-10-30 Added docu for STm32
2013-10-30 Deleted Failed Firmware dir
2013-11-01 imported a lot more stuff, speedoino 2.0 at 35%
2013-11-03 Menu reworked, display running
2013-11-03 Readded Lib Files
2013-11-11 Moved to Chan's-FAT-Lib
2013-11-24 Working SDIO
2013-11-27 Adding STm32F429 to respo
2013-12-01 Before move to SD class
2013-12-02 Added bmp via USB drive
2014-02-23 last update befor pc switch
2014-03-07 Initial Release of SmartSpeedo
2014-03-09 Added new design + gps
2014-03-09 Added init release of SmartSpeedo Firmware
2014-03-11 Moved to Service
2014-03-11 Backup
2014-03-13 Added schematics
2014-03-17 Pre Design change
2014-03-19 Added linear layout 0.1
2014-04-12 SmartSpeedo, added calculation method for voltage devider
2014-04-14 impoved bluetooth setup procedure
2014-04-15 Updated speed class to avoid resets to zero
2014-04-17 Repaired Design (5V Diode)
2014-04-18 SmartSpeedo is able to catch airtemp, rpm and speed reliable
2014-04-20 Added overlay
